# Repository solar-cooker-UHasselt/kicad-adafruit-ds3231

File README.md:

# kicad-adafruit-ds3231

A breakout board for the DS3231, a precision real-time clock with a built-in
temperature-compensated crystal and a CR1220 coin cell that keeps the time without
power. It is a KiCad 10 port of
[Adafruit's DS3231 breakout](https://github.com/adafruit/Adafruit-DS3231-Precision-RTC-Breakout-PCB),
originally drawn in Eagle.

In the [solar cooker](https://github.com/solar-cooker-UHasselt) testing station, the
firmware ([arduino-code](https://github.com/solar-cooker-UHasselt/arduino-code)) reads
the date and time from it over I²C to stamp every measurement and to name the CSV
files on the microSD card.

- [Board page](https://solar-cooker-uhasselt.github.io/kicad-adafruit-ds3231/): 3D
  renders, drawings, schematic and board PDF, interactive BOM and the BOM CSV for
  Eurocircuits, rebuilt by CI on every push to `main`
- [PCB source](https://github.com/adafruit/Adafruit-DS3231-Precision-RTC-Breakout-PCB):
  Adafruit's Eagle files
- [Adafruit guide](https://learn.adafruit.com/adafruit-ds3231-precision-rtc-breakout):
  pinout, wiring and Arduino examples

## Installation

### Requirements

- [KiCad 10](https://www.kicad.org/download/), to open and edit the board
- [git](https://git-scm.com), to clone the repo with its library
- Optional, for the checks: [just](https://just.systems)

### Clone

Own symbols, footprints and 3D models come from
[kicad-common](https://github.com/solar-cooker-UHasselt/kicad-common), a git submodule
at `kicad-common/`. Clone with it:

```bash
git clone --recurse-submodules https://github.com/solar-cooker-UHasselt/kicad-adafruit-ds3231.git
```

Or, in a clone made without it:

```bash
git submodule update --init
```

## Usage

Open `DS3231.kicad_pro` in KiCad 10. The schematic and board open from there.

Before committing, run ERC and DRC (DRC includes the Eurocircuits PCB proto limits),
reports in `tmp/`:

```bash
just check
```

`just --list` shows the other recipes: PDFs, and the CI workflow run locally.

## Contributing

Branches, pull requests, approval and commits work as in every repo of the org, see
[CONTRIBUTING.md](https://github.com/solar-cooker-UHasselt/.github/blob/main/.github/CONTRIBUTING.md).
Specific to this repo:

- CI runs ERC and DRC on every pull request, through the shared workflows in
  [kicad-ci](https://github.com/solar-cooker-UHasselt/kicad-ci). A push to `main` that
  changes more than Markdown also rebuilds the board page.
- Types, scopes and the ERC/DRC check for commits are in
  [.agents/commit_conventions.md](.agents/commit_conventions.md).
- This is the reference repo for the other board repos: a change to the board setup,
  CI or docs is made and tested here first.

## Authors and acknowledgment

The board is Adafruit's design, by Limor Fried/Ladyada for Adafruit Industries
([PCB source](https://github.com/adafruit/Adafruit-DS3231-Precision-RTC-Breakout-PCB)).
The KiCad 10 port is by Lowie Van Vyve for the UHasselt solar cooker project.

Adafruit invests time and resources providing this open source design. Please support
Adafruit and open-source hardware by purchasing products from
[Adafruit](https://www.adafruit.com).

<details>
<summary>Adafruit's original README, included as its license asks</summary>

> **Adafruit DS3231 Precision RTC Breakout PCB**
>
> [Click here to purchase one from the Adafruit shop](http://www.adafruit.com/products/5188)
>
> [Click here to purchase one from the Adafruit shop](http://www.adafruit.com/products/3013)
>
> The datasheet for the DS3231 explains that this part is an "Extremely Accurate
> I²C-Integrated RTC/TCXO/Crystal". And, hey, it does exactly what it says on the tin!
> This Real Time Clock (RTC) is the most precise you can get in a small, low power
> package.
>
> Most RTCs use an external 32kHz timing crystal that is used to keep time with low
> current draw. And that's all well and good, but those crystals have slight drift,
> particularly when the temperature changes (the temperature changes the oscillation
> frequency very very very slightly but it does add up!) This RTC is in a beefy package
> because the crystal is inside the chip! And right next to the integrated crystal is a
> temperature sensor. That sensor compensates for the frequency changes by adding or
> removing clock ticks so that the timekeeping stays on schedule.
>
> This is the finest RTC you can get, and now we have it in a compact,
> breadboard-friendly breakout. With a coin cell plugged into the back, you can get
> years of precision timekeeping, even when main power is lost. Great for datalogging
> and clocks, or anything where you need to really know the time.
>
> PCB files for the Adafruit DS3231 Precision RTC Breakout. The format is EagleCAD
> schematic and board layout
>
> - https://www.adafruit.com/products/3013
>
> **License**
>
> Adafruit invests time and resources providing this open source design, please support
> Adafruit and open-source hardware by purchasing products from
> [Adafruit](https://www.adafruit.com)!
>
> All text above must be included in any redistribution
>
> Designed by Limor Fried/Ladyada for Adafruit Industries. Creative Commons
> Attribution/Share-Alike, all text above must be included in any redistribution. See
> license.txt for additional information.

</details>

## License

[CC BY-SA 4.0](LICENSE). Adafruit's original design is licensed CC BY-SA 3.0, which
allows adaptations like this port under a later version with the same terms.

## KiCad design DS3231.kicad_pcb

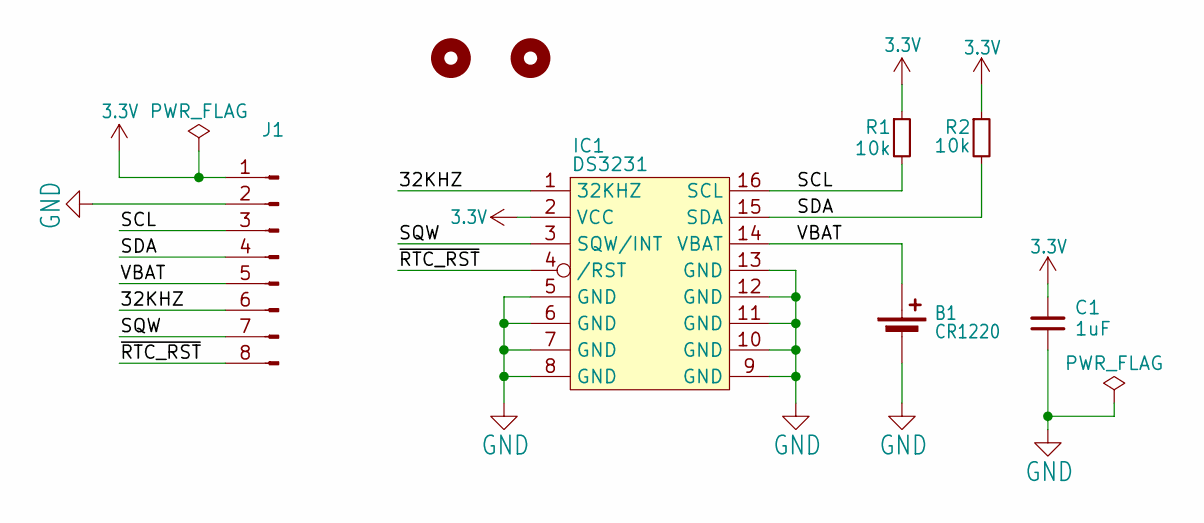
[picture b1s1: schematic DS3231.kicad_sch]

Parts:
B1: CR1220; BatteryHolder_Keystone_3000_1x12mm; MPN 3000
C1: 1uF; C_0805_2012Metric; MPN /
IC1: DS3231; SOIC-16W_7.5x10.3mm_P1.27mm; MPN DS3231M+TRL
J1: Conn_01x08_Pin; PinHeader_1x08_P2.54mm_Vertical; MPN TSW-108-23-G-S
R1, R2: 10k; R_0805_2012Metric; MPN /
U$1, U$2: MOUNTINGHOLE2.5; MountingHole_2.5mm

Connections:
3.3V: C1.2, IC1.2 (VCC), J1.1, R1.1, R2.1
/32KHZ: IC1.1 (32KHZ), J1.6
/SCL: IC1.16 (SCL), J1.3, R1.2
/SDA: IC1.15 (SDA), J1.4, R2.2
/SQW: IC1.3 (SQW/INT), J1.7
/VBAT: B1.1 (+), IC1.14 (VBAT), J1.5
/~RTC_RST: IC1.4 (/RST), J1.8
GND: B1.2 (-), C1.1, IC1.5 (GND), IC1.6 (GND), IC1.7 (GND), IC1.8 (GND), IC1.9 (GND), IC1.10 (GND), IC1.11 (GND), IC1.12 (GND), IC1.13 (GND), J1.2

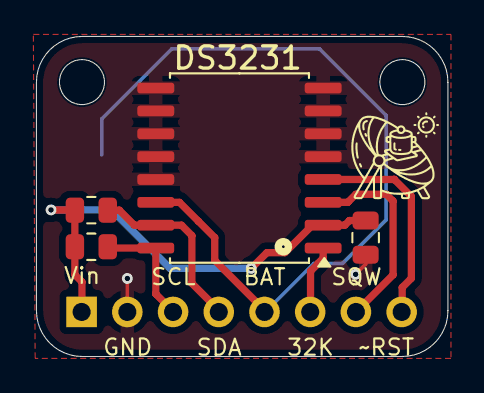
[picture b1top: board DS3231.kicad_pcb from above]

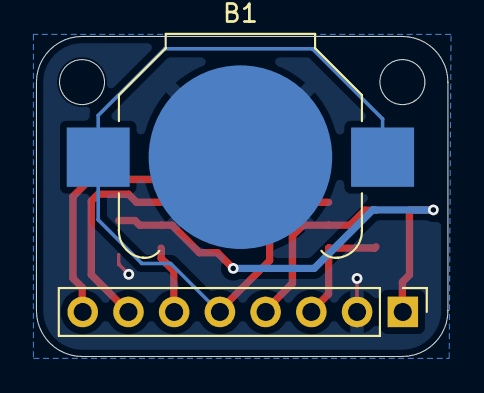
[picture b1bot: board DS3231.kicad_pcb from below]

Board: 2 copper layers, 22.9 x 17.8 mm, 8 parts (2 on the bottom side), 8 nets.

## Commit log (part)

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2024-03-05 .gitignore update
2024-03-05 blank KiCad project
2024-03-05 Eagle import
2024-03-06 added drawing sheet
2024-03-06 fully migrated to KiCad
2024-03-06 added info to generate BOM file
2024-03-07 fixed incorrect item in BOM
2024-04-01 updated routing + symbol update
2024-04-01 silkscreen + routing update
2024-04-01 added ground plane front and bottom
2024-04-01 production ready
2024-04-03 removed unused copper layers
2024-04-03 changed copper finish + solder mask and silkscreen color update
2024-04-04 KiBot DRC check workflow
2024-04-05 project update
2024-05-02 changed pin header orientation
2024-05-21 CR1220 footprint update
2024-06-10 BOM presets update
